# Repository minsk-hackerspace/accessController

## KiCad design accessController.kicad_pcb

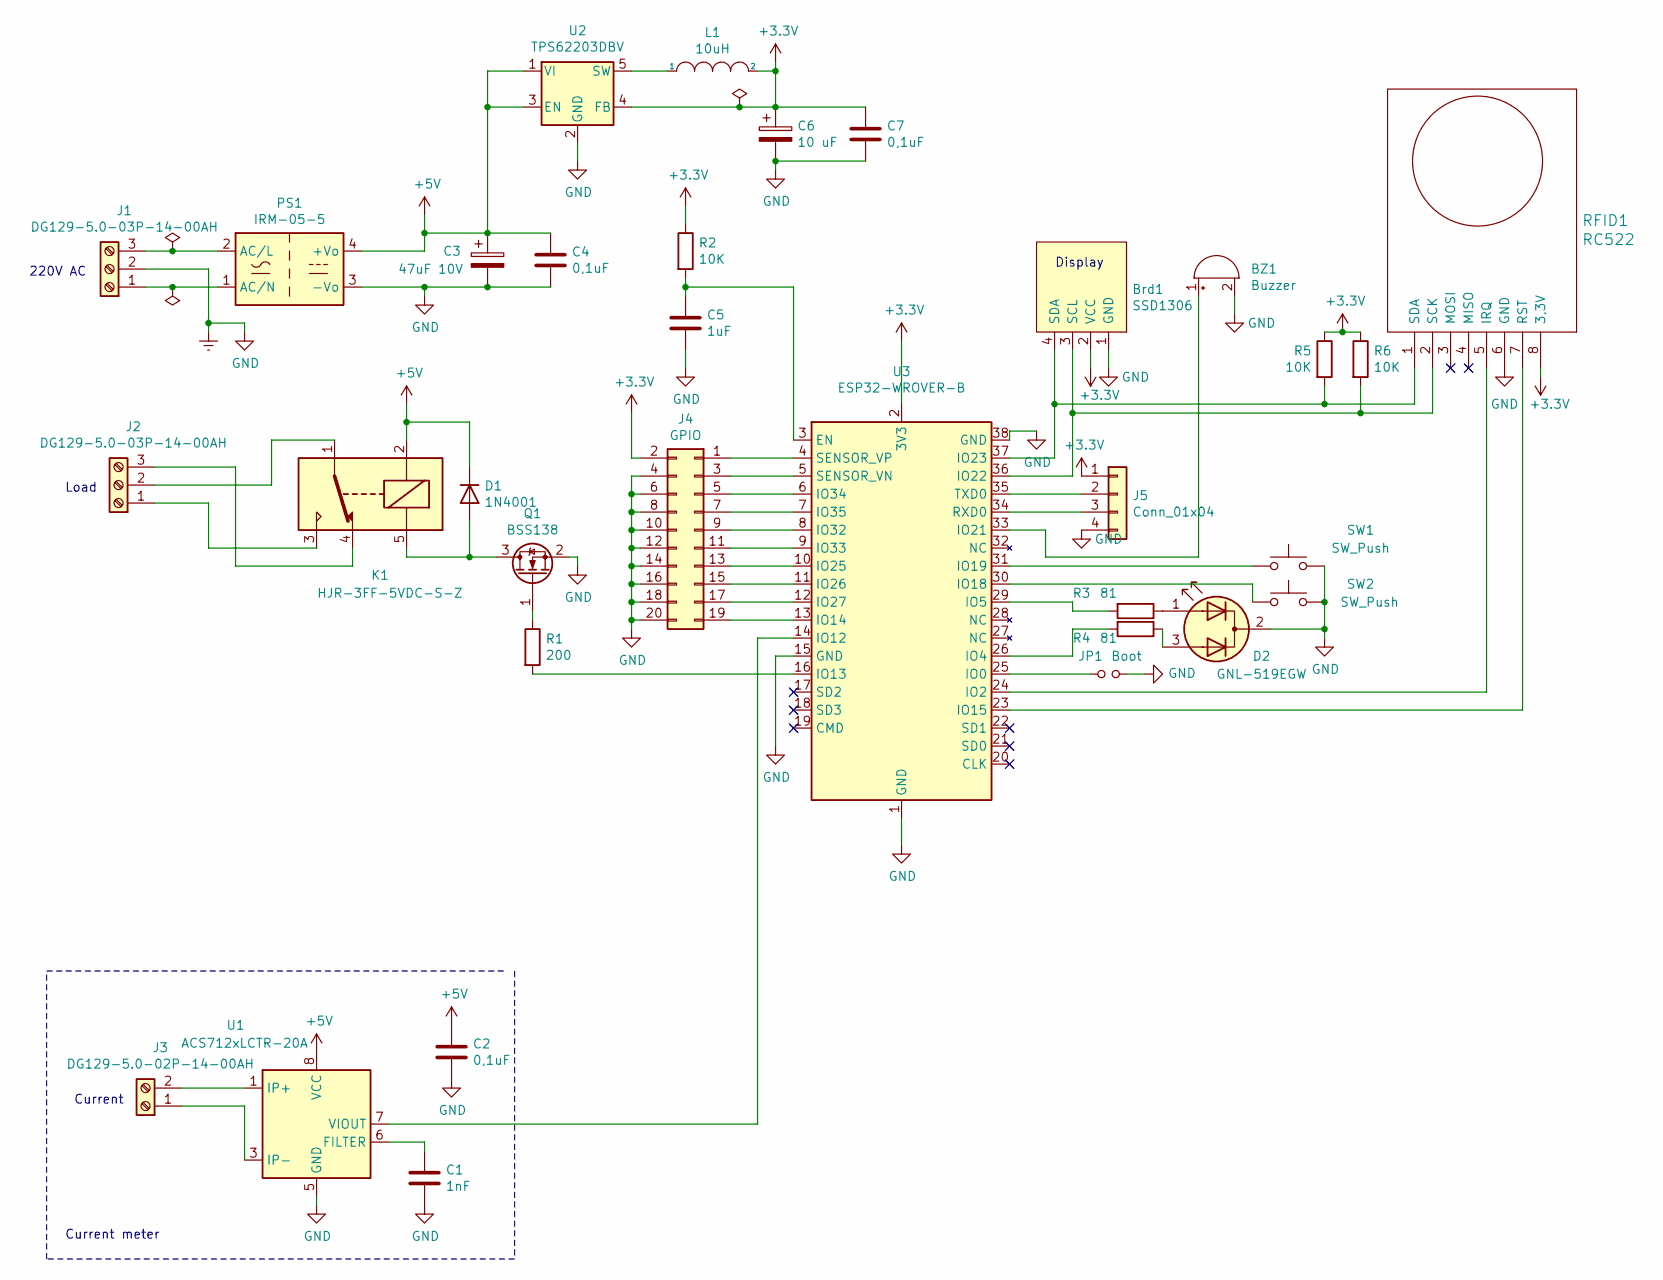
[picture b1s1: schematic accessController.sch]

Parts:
BZ1: Buzzer; Buzzer_12x9.5RM7.6
Brd1: SSD1306; PinHeader_1x04_P2.54mm_Vertical
C1: 1nF; C_0805_2012Metric
C2, C4, C7: 0,1uF; C_0805_2012Metric
C3: 47uF 10V; CP_EIA-3528-21_Kemet-B
C5: 1uF; C_0805_2012Metric
C6: 10 uF; CP_EIA-3528-21_Kemet-B
D1: 1N4001; D_DO-41_SOD81_P10.16mm_Horizontal
D2: GNL-519EGW; LED_D5.0mm-3
J1, J2: DG129-5.0-03P-14-00AH; TerminalBlock_Altech_AK300-3_P5.00mm
J3: DG129-5.0-02P-14-00AH; TerminalBlock_Altech_AK300-2_P5.00mm
J4: GPIO; PinHeader_2x10_P2.54mm_Vertical
J5: Conn_01x04; PinHeader_1x04_P2.54mm_Vertical
JP1: Boot; PinHeader_1x02_P2.54mm_Vertical
K1: HJR-3FF-5VDC-S-Z; Relay_SPDT_HJR-3FF
L1: 10uH; L_Murata_LQH55DN_5.7x5.0mm
PS1: IRM-05-5; Converter_ACDC_MeanWell_IRM-05-xx_THT
Q1: BSS138; SOT-23
R1: 200; R_0805_2012Metric
R2, R5, R6: 10K; R_0805_2012Metric
R3, R4: 81; R_0805_2012Metric
RFID1: RC522; PinHeader_1x08_P2.54mm_Vertical
SW1, SW2: SW_Push; SW_PUSH_6mm_H5mm
U1: ACS712xLCTR-20A; SOIC-8_3.9x4.9mm_P1.27mm
U2: TPS62203DBV; SOT-23-5
U3: ESP32-WROVER-B

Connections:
+3V3: Brd1.2 (VCC), C6.1, C7.1, J4.2, J5.1, L1.2, R2.1, R5.1, R6.1, RFID1.8 (3,3V), U2.4 (FB), U3.2 (3V3)
+5V: C2.1, C3.1, C4.1, D1.1 (K), K1.2, PS1.4 (+Vo), U1.8 (VCC), U2.1 (VI), U2.3 (EN)
Earth: BZ1.2 (+), Brd1.1 (GND), C1.2, C2.2, C3.2, C4.2, C5.2, C6.2, C7.2, D2.2 (K), J1.2, J4.4, J4.6, J4.8, J4.10, J4.12, J4.14, J4.16, J4.18, J4.20, J5.4, JP1.2, PS1.3 (-Vo), Q1.2 (S), RFID1.6 (GND), SW1.2, SW2.2, U1.5 (GND), U2.2 (GND), U3.1 (GND), U3.15 (GND), U3.38 (GND), U3.39 (GND)
unnamed: BZ1.1 (-), U3.33 (IO21)
unnamed: Brd1.3 (SCL), R6.2, RFID1.2 (SCK), U3.36 (IO22)
unnamed: Brd1.4 (SDA), R5.2, RFID1.1 (SDA), U3.37 (IO23)
unnamed: C1.1, U1.6 (FILTER)
unnamed: C5.1, R2.2, U3.3 (EN)
unnamed: D1.2 (A), K1.5, Q1.3 (D)
unnamed: D2.1 (A1), R3.1
unnamed: D2.3 (A2), R4.1
unnamed: J1.1, PS1.1 (AC/N)
unnamed: J1.3, PS1.2 (AC/L)
unnamed: J2.1, K1.3
unnamed: J2.2, K1.1
unnamed: J2.3, K1.4
unnamed: J3.1, U1.3 (IP-), U1.4 (IP-)
unnamed: J3.2, U1.1 (IP+), U1.2 (IP+)
unnamed: J4.1, U3.4 (SENSOR_VP)
unnamed: J4.3, U3.5 (SENSOR_VN)
unnamed: J4.5, U3.6 (IO34)
unnamed: J4.7, U3.7 (IO35)
unnamed: J4.9, U3.8 (IO32)
unnamed: J4.11, U3.9 (IO33)
unnamed: J4.13, U3.10 (IO25)
unnamed: J4.15, U3.11 (IO26)
unnamed: J4.17, U3.12 (IO27)
unnamed: J4.19, U3.13 (IO14)
unnamed: J5.2, U3.35 (TXD0)
unnamed: J5.3, U3.34 (RXD0)
unnamed: JP1.1, U3.25 (IO0)
unnamed: L1.1, U2.5 (SW)
unnamed: Q1.1 (G), R1.1
unnamed: R1.2, U3.16 (IO13)
unnamed: R3.2, U3.29 (IO5)
unnamed: R4.2, U3.26 (IO4)
unnamed: RFID1.5 (IRQ), U3.24 (IO2)
unnamed: RFID1.7 (RST), U3.23 (IO15)
unnamed: SW1.1, U3.31 (IO19)
unnamed: SW2.1, U3.30 (IO18)
unnamed: U1.7 (VIOUT), U3.14 (IO12)

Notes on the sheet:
Display
Current meter
220V AC
Load
Current

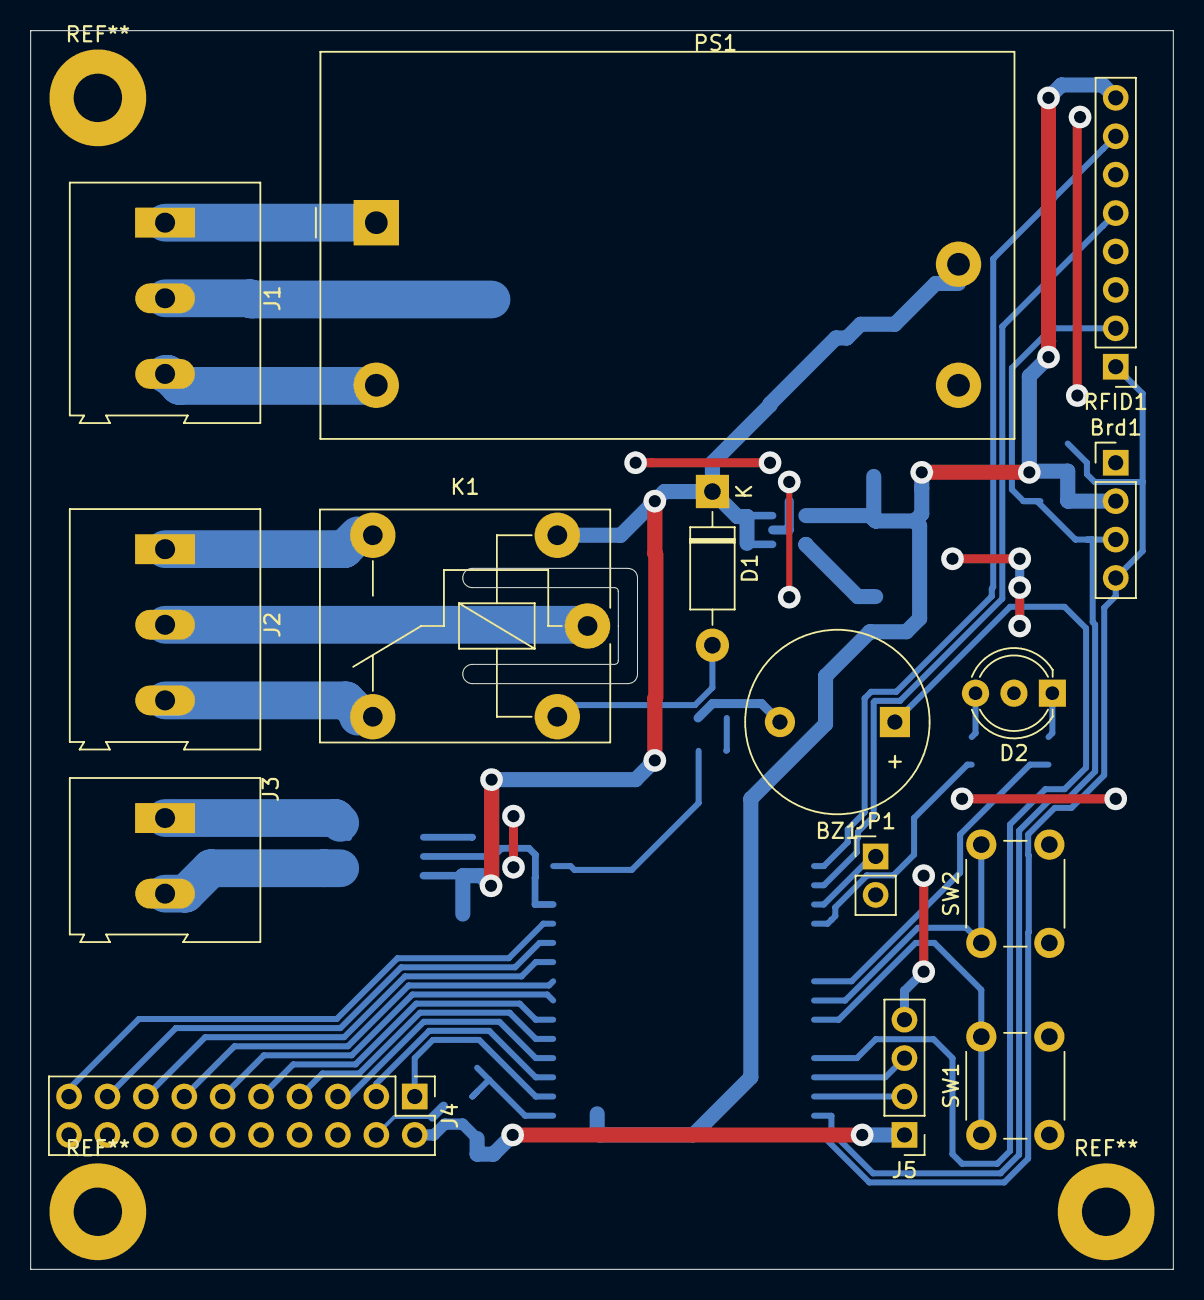
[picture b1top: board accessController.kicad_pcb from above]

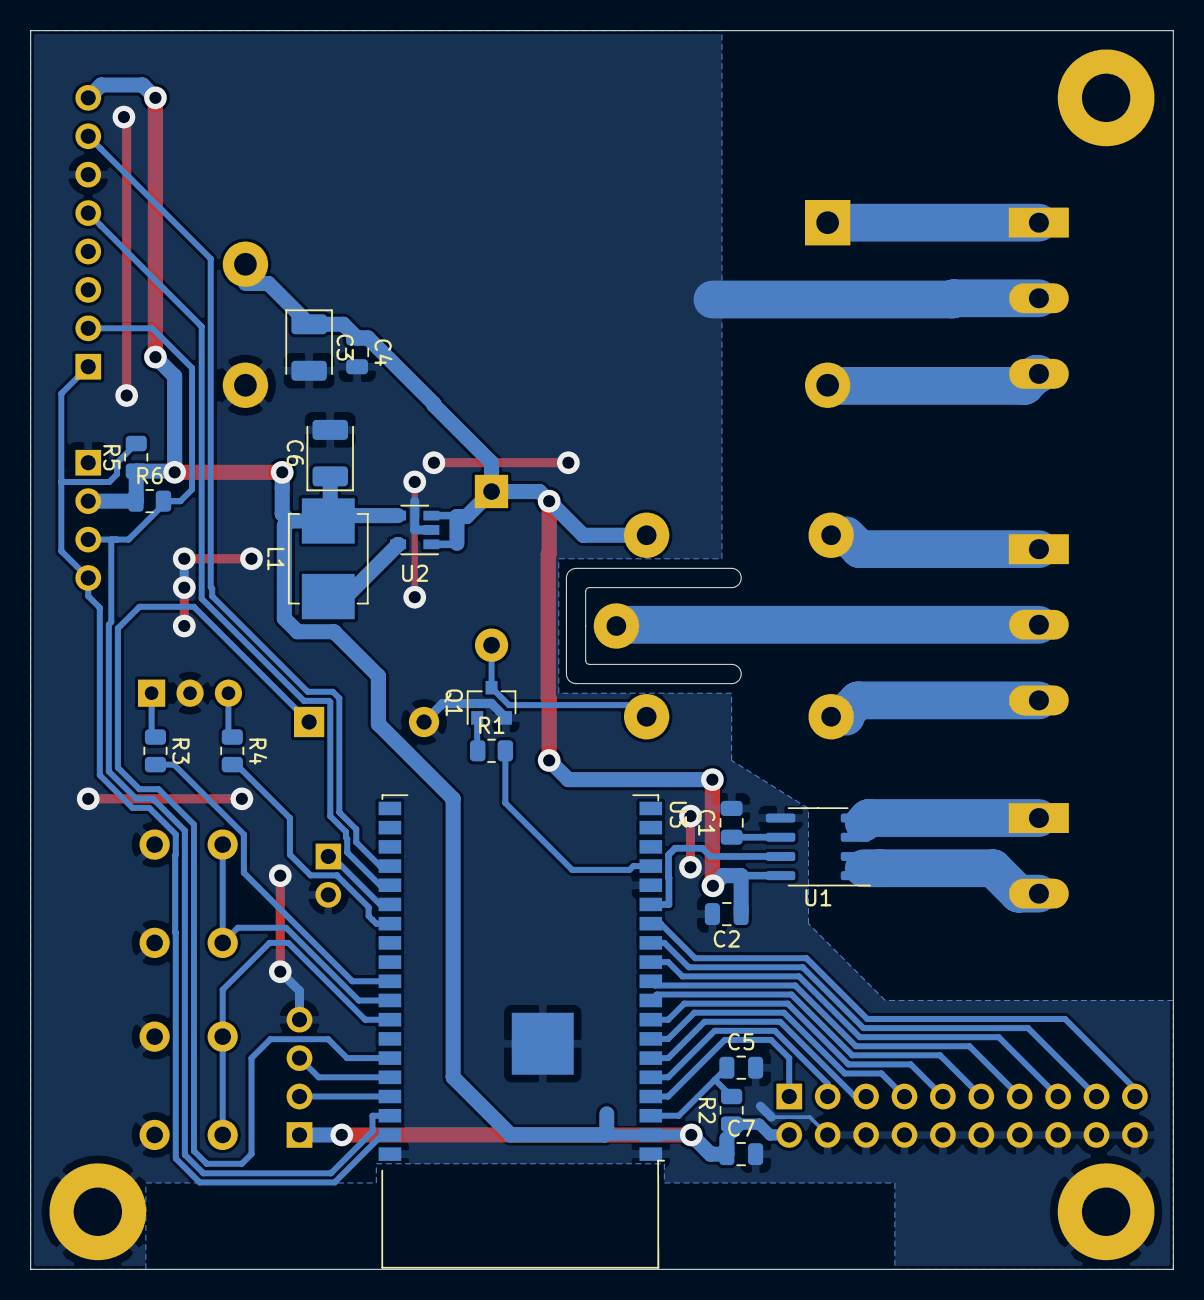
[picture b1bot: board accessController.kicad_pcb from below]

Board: 2 copper layers, 75.6 x 81.9 mm, 33 parts (18 on the bottom side), 41 nets.

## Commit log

2021-04-26 Update, reduce unfilled zones for easier milling
2021-04-27 Update slot
